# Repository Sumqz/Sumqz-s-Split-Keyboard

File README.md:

# Sumqz-s-Split-Keyboard

## NOTE TO REVIEWER FROM BLUEPRINT: Because the projects exceeds the 100 dollar price limit of T3 projects i am willing to pay the additional 50 dollars needed. I am happy with a partial grant!

Hey everyone, this is my split keyboard project.

I always felt that traditional keyboards were functional but boring, so I decided to build my own. It can work as two separate halves or snap together with magnets to become a full 75% style keyboard in seconds.

It is hot-swappable, uses nRF52840 boards, and is designed to be easy to build at home.

I sanity-checked this design with my friend before finalizing it.

## Short Description

A DIY wireless split keyboard with magnetic attachment and hot-swap sockets.

## Pictures

## Bill of Materials

| Part | Qty | Notes | Link |
|---|---:|---|---|
| nRF52840 (XIAO nRF52840) | 2 | One per side | [Buy](https://it.aliexpress.com/item/1005006988954136.html) |
| MCP23017 GPIO Expander | 2 | MCP23017_SP, DIP-28 package required | [Buy](https://it.aliexpress.com/item/1005009603989894.html) |
| LiPo 1200mAh | 2 | One per side | [Buy](https://it.aliexpress.com/item/1005011550469394.html) |
| Buzzer 12x9.5 / RM7.6 | 2 | Match PCB footprint pin spacing | [Buy](https://it.aliexpress.com/item/1005002576043967.html) |
| Switches (Holy Panda) | 87 | Total keys | [Buy](https://it.aliexpress.com/item/1005004388563696.html) |
| Keycaps (generic) | 87 | Match your layout | [Buy](https://it.aliexpress.com/item/1005011879391386.html) |
| Diodes 1N4148W (SOD-123) | 87 | One per switch | [Buy](https://it.aliexpress.com/item/1005003194674618.html) |
| Resistor 4.7k (0805) | 4 | R1, R2, R5, R6 | [Buy](https://it.aliexpress.com/item/1005011649990763.html) |
| Resistor 806k (0805) | 2 | R3, R7 | [Buy](https://it.aliexpress.com/item/1005011649990763.html) |
| Resistor 2M (0805) | 2 | R4, R8 | [Buy](https://it.aliexpress.com/item/1005011649990763.html) |
| Magnets 6x2 | 8 | 2 per hole | [Buy](https://it.aliexpress.com/item/1005009677185619.html) |
| M3 screw + nut | 4 | 40 mm | [Buy](https://it.aliexpress.com/item/1005008625463950.html) |
| M4 screw | 4 | 50 mm | [Buy](https://it.aliexpress.com/item/1005008625463950.html) |
| M4 nut | 4 | M4 | [Buy](https://it.aliexpress.com/item/1005010329406193.html) |
| Hotswap sockets | 87 | choc | [But](https://it.aliexpress.com/item/1005008543325730.html)

# Total price: about 150 euros or 167 dollars

PCB and case are not included because they are custom-made.

Resistor note: it is usually cheaper to buy one full 0805 resistor assortment than to buy each value separately.

## How to Use

Flash the `.ino` firmware to both nRF52840 boards. Then connect each half to your PC and test that every key works.

You can use it as a split keyboard, or snap both halves together with magnets to use it like a full 75% style board.

## Firmware

Firmware source: `Firmware/SplitKeyboard/SplitKeyboard.ino`

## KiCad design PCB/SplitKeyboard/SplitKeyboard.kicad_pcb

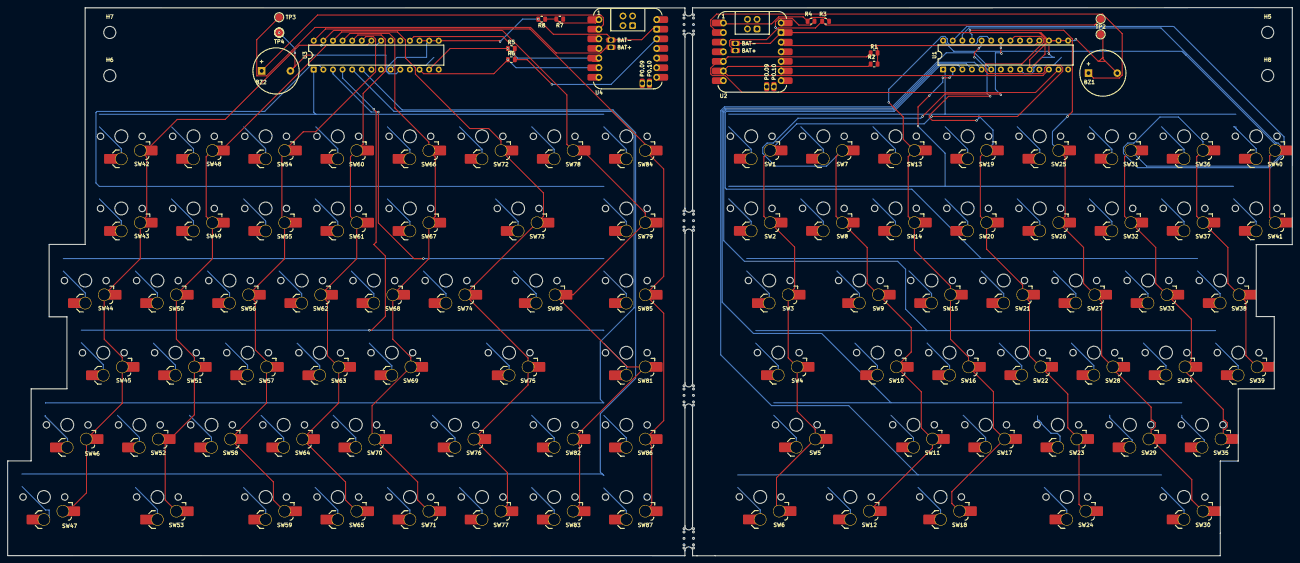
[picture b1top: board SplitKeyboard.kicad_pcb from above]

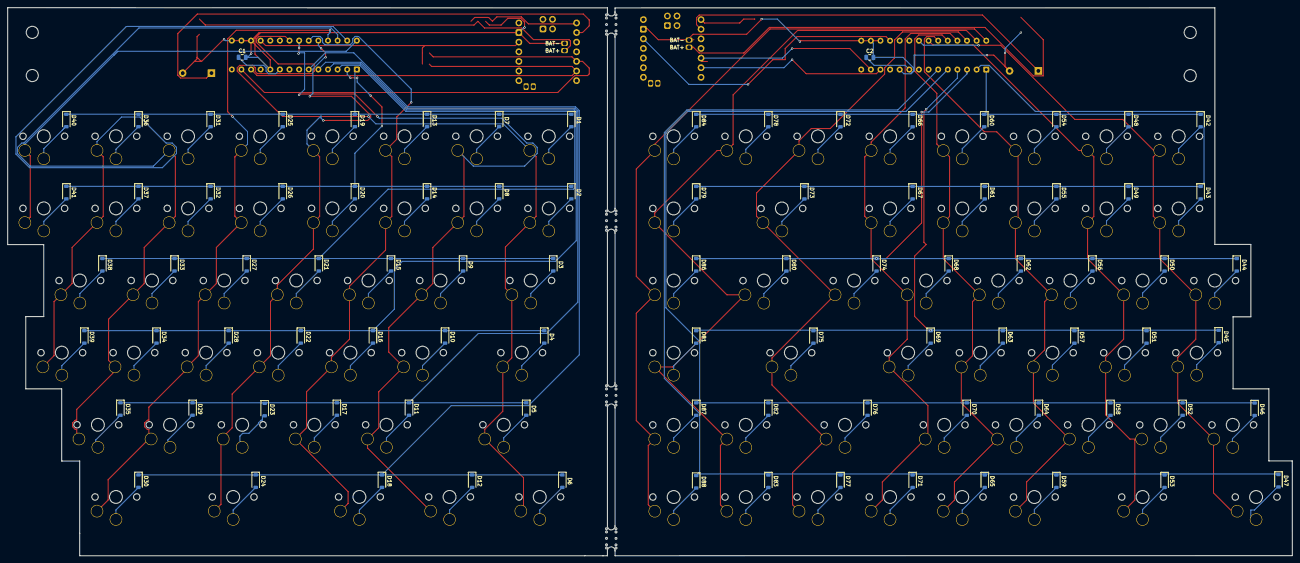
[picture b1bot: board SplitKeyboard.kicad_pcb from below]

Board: 2 copper layers, 339.2 x 144.7 mm, 203 parts (89 on the bottom side), 129 nets.

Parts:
B2, B3, B4, B8: MouseBite; MouseBite-Slot_2.0x4.5mm_inset_D0.5mm_P0.85mm_5h_Trace
BZ1, BZ2: Buzzer; Buzzer_12x9.5RM7.6
C1, C2: 100nF c.Cap.; C_0805_2012Metric
D1, D2, D3, D4, D5, D6, D7, D8, D9, D10, D11, D12, D13, D14, D15, D16, D17, D18, D19, D20, D21, D22, D23, D24, D25, D26, D27, D28, D29, D30, D31, D32, D33, D34, D35, D36, D37, D38, D39, D40, D41, D42, D43, D44, D45, D46, D47, D48, D49, D50, D51, D52, D53, D54, D55, D56, D57, D58, D59, D60, D61, D62, D63, D64, D65, D66, D67, D68, D69, D70, D71, D72, D73, D74, D75, D76, D77, D78, D79, D80, D81, D82, D83, D84, D86, D87, D88: D; D_SOD-123
H5, H6, H7, H8: MountingHole; MountingHole_3.2mm_M3
R1, R2, R5, R6: 4.7K; R_0805_2012Metric
R3, R7: 806K; R_0805_2012Metric
R4, R8: 2M; R_0805_2012Metric
SW1, SW2, SW7, SW8, SW9, SW10, SW11, SW13, SW14, SW15, SW16, SW17, SW19, SW20, SW21, SW22, SW23, SW25, SW26, SW27, SW28, SW29, SW30, SW31, SW32, SW33, SW34, SW35, SW36, SW37, SW38, SW39, SW40, SW41, SW42, SW43, SW44, SW45, SW46, SW47, SW48, SW49, SW50, SW51, SW52, SW53, SW54, SW55, SW56, SW57, SW58, SW59, SW60, SW61, SW62, SW63, SW64, SW65, SW66, SW67, SW68, SW69, SW70, SW71, SW72, SW73, SW74, SW77, SW78, SW79, SW81, SW82, SW83, SW84, SW85, SW86, SW87: SW_Push; SW_choc_v1_HS_CPG135001S30_1u
SW3, SW80: SW_Push; SW_choc_v1_HS_CPG135001S30_1.5u
SW4, SW76: SW_Push; SW_choc_v1_HS_CPG135001S30_1.75u
SW5, SW24, SW75: SW_Push; SW_choc_v1_HS_CPG135001S30_2.25u
SW6, SW12, SW18: SW_Push; SW_choc_v1_HS_CPG135001S30_1.25u
TP1, TP2, TP2#2, TP3, TP4: TestPoint; TestPoint_Pad_D2.0mm
U1, U3: MCP23017_SP; DIP-28_W7.62mm
U2, U4: Seeeduino Xiao nRF52840; Xiao_nRF52840_ACH

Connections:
+3V3: R1.2, R2.2, R5.2, R6.2, U1.18 (~RESET), U2.10 (3V3), U3.18 (~RESET), U4.10 (3V3)
/left/3V3: C1.1, U1.9 (VDD)
/left/BT_PIN: R3.2, R4.1, U2.1 (P0.02)
/left/BZ_PIN: BZ1.1 (+), U2.2 (P0.03)
/left/Col0: SW1.1, SW2.1, SW3.1, SW4.1, SW5.1, SW6.1, U1.21 (GPA0)
/left/Col1: SW7.1, SW8.1, SW9.1, SW10.1, SW11.1, SW12.1, U1.22 (GPA1)
/left/Col2: SW13.1, SW14.1, SW15.1, SW16.1, SW17.1, SW18.1, U1.23 (GPA2)
/left/Col3: SW19.1, SW20.1, SW21.1, SW22.1, SW23.1, SW24.1, U1.24 (GPA3)
/left/Col4: SW25.1, SW26.1, SW27.1, SW28.1, SW29.1, SW30.1, U1.25 (GPA4)
/left/Col5: SW31.1, SW32.1, SW33.1, SW34.1, SW35.1, U1.26 (GPA5)
/left/Col6: SW36.1, SW37.1, SW38.1, SW39.1, U1.27 (GPA6)
/left/Col7: SW40.1, SW41.1, U1.28 (GPA7)
/left/Row0: D1.1 (K), D7.1 (K), D13.1 (K), D19.1 (K), D25.1 (K), D31.1 (K), D36.1 (K), D40.1 (K), U1.1 (GPB0)
/left/Row1: D2.1 (K), D8.1 (K), D14.1 (K), D20.1 (K), D26.1 (K), D32.1 (K), D37.1 (K), D41.1 (K), U1.2 (GPB1)
/left/Row2: D3.1 (K), D9.1 (K), D15.1 (K), D21.1 (K), D27.1 (K), D33.1 (K), D38.1 (K), U1.3 (GPB2)
/left/Row3: D4.1 (K), D10.1 (K), D16.1 (K), D22.1 (K), D28.1 (K), D34.1 (K), D39.1 (K), U1.4 (GPB3)
/left/Row4: D5.1 (K), D11.1 (K), D17.1 (K), D23.1 (K), D29.1 (K), D35.1 (K), U1.5 (GPB4)
/left/Row5: D6.1 (K), D12.1 (K), D18.1 (K), D24.1 (K), D30.1 (K), U1.6 (GPB5)
/left/SCK: R2.1, U1.12 (SCK), U2.6 (P0.05)
/left/SDA: R1.1, U1.13 (SDA), U2.5 (P0.04)
/left/VBAT: R3.1, TP1.1, U2.16 (BAT+)
/right/3V3: C2.1, U3.9 (VDD)
/right/BT_PIN2: R7.2, R8.1, U4.1 (P0.02)
/right/BZ_PIN2: BZ2.1 (+), U4.2 (P0.03)
/right/Col0: SW42.1, SW43.1, SW44.1, SW45.1, SW46.1, SW47.1, U3.21 (GPA0)
/right/Col1: SW48.1, SW49.1, SW50.1, SW51.1, SW52.1, SW53.1, U3.22 (GPA1)
/right/Col2: SW54.1, SW55.1, SW56.1, SW57.1, SW58.1, SW59.1, U3.23 (GPA2)
/right/Col3: SW60.1, SW61.1, SW62.1, SW63.1, SW64.1, SW65.1, U3.24 (GPA3)
/right/Col4: SW66.1, SW67.1, SW68.1, SW69.1, SW70.1, SW71.1, U3.25 (GPA4)
/right/Col5: SW72.1, SW73.1, SW74.1, SW75.1, SW76.1, SW77.1, U3.26 (GPA5)
/right/Col6: SW78.1, SW79.1, SW80.1, SW81.1, SW82.1, SW83.1, U3.27 (GPA6)
/right/Col7: SW84.1, SW85.1, SW86.1, SW87.1, U3.28 (GPA7)
/right/Row0: D42.1 (K), D48.1 (K), D54.1 (K), D60.1 (K), D66.1 (K), D72.1 (K), D78.1 (K), D84.1 (K), U3.1 (GPB0)
/right/Row1: D43.1 (K), D49.1 (K), D55.1 (K), D61.1 (K), D67.1 (K), D73.1 (K), D79.1 (K), U3.2 (GPB1)
/right/Row2: D44.1 (K), D50.1 (K), D56.1 (K), D62.1 (K), D68.1 (K), D74.1 (K), D80.1 (K), D86.1 (K), U3.3 (GPB2)
/right/Row3: D45.1 (K), D51.1 (K), D57.1 (K), D63.1 (K), D69.1 (K), D75.1 (K), D81.1 (K), U3.4 (GPB3)
/right/Row4: D46.1 (K), D52.1 (K), D58.1 (K), D64.1 (K), D70.1 (K), D76.1 (K), D82.1 (K), D87.1 (K), U3.5 (GPB4)
/right/Row5: D47.1 (K), D53.1 (K), D59.1 (K), D65.1 (K), D71.1 (K), D77.1 (K), D83.1 (K), D88.1 (K), U3.6 (GPB5)
/right/SCK2: R6.1, U3.12 (SCK), U4.6 (P0.05)
/right/SDA2: R5.1, U3.13 (SDA), U4.5 (P0.04)
/right/VBAT2: TP3.1, U4.16 (BAT+)
GND: BZ1.2 (-), BZ2.2 (-), C1.2, C2.2, R4.2, R8.2, TP2.1, TP2#2.1, TP4.1, U1.10 (VSS), U1.15 (A0), U1.16 (A1), U1.17 (A2), U2.9 (GND), U2.15 (BAT-), U3.10 (VSS), U3.15 (A0), U3.16 (A1), U3.17 (A2), U4.9 (GND), U4.15 (BAT-)
unnamed: D1.2 (A), SW1.2
unnamed: D2.2 (A), SW2.2
unnamed: D3.2 (A), SW3.2
unnamed: D4.2 (A), SW4.2
unnamed: D5.2 (A), SW5.2
unnamed: D6.2 (A), SW6.2
unnamed: D7.2 (A), SW7.2
unnamed: D8.2 (A), SW8.2
unnamed: D9.2 (A), SW9.2
unnamed: D10.2 (A), SW10.2
unnamed: D11.2 (A), SW11.2
unnamed: D12.2 (A), SW12.2
unnamed: D13.2 (A), SW13.2
unnamed: D14.2 (A), SW14.2
unnamed: D15.2 (A), SW15.2
unnamed: D16.2 (A), SW16.2
unnamed: D17.2 (A), SW17.2
unnamed: D18.2 (A), SW18.2
unnamed: D19.2 (A), SW19.2
unnamed: D20.2 (A), SW20.2
unnamed: D21.2 (A), SW21.2
unnamed: D22.2 (A), SW22.2
unnamed: D23.2 (A), SW23.2
unnamed: D24.2 (A), SW24.2
unnamed: D25.2 (A), SW25.2
unnamed: D26.2 (A), SW26.2
unnamed: D27.2 (A), SW27.2
unnamed: D28.2 (A), SW28.2
unnamed: D29.2 (A), SW29.2
unnamed: D30.2 (A), SW30.2
unnamed: D31.2 (A), SW31.2
unnamed: D32.2 (A), SW32.2
unnamed: D33.2 (A), SW33.2
unnamed: D34.2 (A), SW34.2
unnamed: D35.2 (A), SW35.2
unnamed: D36.2 (A), SW36.2
unnamed: D37.2 (A), SW37.2
unnamed: D38.2 (A), SW38.2
unnamed: D39.2 (A), SW39.2
unnamed: D40.2 (A), SW40.2
unnamed: D41.2 (A), SW41.2
unnamed: D42.2 (A), SW42.2
unnamed: D43.2 (A), SW43.2
unnamed: D44.2 (A), SW44.2
unnamed: D45.2 (A), SW45.2
unnamed: D46.2 (A), SW46.2
unnamed: D47.2 (A), SW47.2
unnamed: D48.2 (A), SW48.2
unnamed: D49.2 (A), SW49.2
unnamed: D50.2 (A), SW50.2
unnamed: D51.2 (A), SW51.2
unnamed: D52.2 (A), SW52.2
unnamed: D53.2 (A), SW53.2
unnamed: D54.2 (A), SW54.2
unnamed: D55.2 (A), SW55.2
unnamed: D56.2 (A), SW56.2
unnamed: D57.2 (A), SW57.2
unnamed: D58.2 (A), SW58.2
unnamed: D59.2 (A), SW59.2
unnamed: D60.2 (A), SW60.2
unnamed: D61.2 (A), SW61.2
unnamed: D62.2 (A), SW62.2
unnamed: D63.2 (A), SW63.2
unnamed: D64.2 (A), SW64.2
unnamed: D65.2 (A), SW65.2
unnamed: D66.2 (A), SW66.2
unnamed: D67.2 (A), SW67.2
unnamed: D68.2 (A), SW68.2
unnamed: D69.2 (A), SW69.2
unnamed: D70.2 (A), SW70.2
unnamed: D71.2 (A), SW71.2
unnamed: D72.2 (A), SW72.2
unnamed: D73.2 (A), SW73.2
unnamed: D74.2 (A), SW74.2
unnamed: D75.2 (A), SW75.2
unnamed: D76.2 (A), SW76.2
unnamed: D77.2 (A), SW77.2
unnamed: D78.2 (A), SW78.2
unnamed: D79.2 (A), SW79.2
unnamed: D80.2 (A), SW80.2
unnamed: D81.2 (A), SW81.2
unnamed: D82.2 (A), SW82.2
unnamed: D83.2 (A), SW83.2
unnamed: D84.2 (A), SW84.2
unnamed: D86.2 (A), SW85.2
unnamed: D87.2 (A), SW86.2
unnamed: D88.2 (A), SW87.2

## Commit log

2026-03-31 Auto-sync: $(date)
2026-03-31 auto sync 2026-03-31 18:37:32
2026-03-31 auto sync 2026-03-31 18:38:52
2026-03-31 auto sync 2026-03-31 18:38:03
2026-03-31 auto sync 2026-03-31 18:43:00
2026-03-31 auto sync 2026-03-31 18:53:26
2026-03-31 Enhance README with additional details and images
    Added short description, pictures, and firmware section to README.
2026-03-31 auto sync 2026-03-31 19:08:52
2026-03-31 auto sync 2026-03-31 19:43:27
2026-03-31 auto sync 2026-03-31 19:48:27
2026-03-31 auto sync 2026-03-31 20:03:27
2026-03-31 auto sync 2026-03-31 20:13:27
2026-03-31 Add Hotswap sockets to the materials list
2026-03-31 Include latest local file changes
